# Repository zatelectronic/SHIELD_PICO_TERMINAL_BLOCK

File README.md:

<div align="center">

# SHIELD PICO TERMINAL BLOCK V1

**Shield de expansão para Raspberry Pi Pico com todos os pinos expostos em bornes de parafuso KRE — conexão fácil e robusta sem solda de fios**

</div>

---

## 📋 Índice

- [SHIELD PICO TERMINAL BLOCK V1](#shield-pico-terminal-block-v1)
  - [📋 Índice](#-índice)
  - [Visão Geral](#visão-geral)
  - [Renders 3D](#renders-3d)
  - [Funcionalidades](#funcionalidades)
  - [Mapa Completo de Pinos](#mapa-completo-de-pinos)
    - [J1 — Borne Esquerdo (20 terminais)](#j1--borne-esquerdo-20-terminais)
    - [J2 — Borne Direito (20 terminais)](#j2--borne-direito-20-terminais)
  - [Especificações Técnicas](#especificações-técnicas)
  - [Lista de Materiais](#lista-de-materiais)
  - [Aplicações](#aplicações)
  - [Estrutura do Repositório](#estrutura-do-repositório)
  - [Como Usar](#como-usar)
    - [Instalação](#instalação)
    - [Alimentação](#alimentação)
    - [Exemplo — Piscar LED interno com MicroPython](#exemplo--piscar-led-interno-com-micropython)
    - [Exemplo — Leitura analógica (GP26\_A0)](#exemplo--leitura-analógica-gp26_a0)
    - [Exemplo — I2C com MicroPython](#exemplo--i2c-com-micropython)
    - [Fixação em painel](#fixação-em-painel)
  - [Sobre](#sobre)

---

## Visão Geral

**SHIELD PICO TERMINAL BLOCK V1** é uma placa de expansão para o **Raspberry Pi Pico (RP2040)**, projetada pela **ZAT ELECTRONIC** utilizando **KiCad 10**. O shield encaixa o Raspberry Pi Pico em dois conectores fêmea de 20 pinos e expõe **todos os 40 pinos** do Pico em **dois bornes de parafuso KRE de 20 terminais cada** — um em cada lateral da placa.

O objetivo é simples e prático: eliminar a necessidade de soldar fios diretamente ao Pico, proporcionando **conexões robustas por parafuso** ideais para prototipagem, automação, laboratório e projetos onde os fios precisam ser trocados com frequência.

> 💡 Todos os pinos do Raspberry Pi Pico são acessíveis diretamente pelos bornes — GP0 a GP28, entradas analógicas A0–A2, alimentações VBUS, VSYS, 3V3, GND, ADC_VREF, AGND, 3V3_EN e RUN.

---

## Renders 3D

<div align="center">

*Vista superior — Raspberry Pi Pico encaixado, bornes KRE nas laterais com serigrafias de todos os pinos*

<br/>

*Vista isométrica — bornes de 20 terminais em cada lado e 4 furos de fixação*

</div>

---

## Funcionalidades

- ✅ **Raspberry Pi Pico (RP2040)** — encaixe via 2 conectores fêmea de 20 pinos 2,54mm
- ✅ **Borne KRE J1** — 20 terminais parafuso, lado esquerdo (GP0–GP15 + GNDs)
- ✅ **Borne KRE J2** — 20 terminais parafuso, lado direito (GP16–GP28 + alimentações)
- ✅ **Todos os 40 pinos expostos** — GPIO, analógicos, alimentação e controle
- ✅ **Pinos de alimentação acessíveis** — VBUS, VSYS, 3V3_OUT, 3V3_EN, ADC_VREF, AGND
- ✅ **Pino RUN acessível** — reset externo do Pico por borne
- ✅ **4 furos de fixação** (H1–H4) — montagem em painel ou caixa
- ✅ **Serigrafias completas** — nome de cada pino impresso ao lado do borne correspondente
- ✅ **Sem componentes adicionais** — shield passivo de conexão pura
- ✅ **Made in Brazil** — serigrafia na PCB

---

## Mapa Completo de Pinos

### J1 — Borne Esquerdo (20 terminais)

| Terminal | Pino Pico | Função |
|----------|-----------|--------|
| 1 | GP0 | GPIO / UART0 TX / SPI0 RX / I2C0 SDA / PWM0A |
| 2 | GP1 | GPIO / UART0 RX / SPI0 CSn / I2C0 SCL / PWM0B |
| 3 | GND | Terra |
| 4 | GP2 | GPIO / SPI0 SCK / I2C1 SDA / PWM1A |
| 5 | GP3 | GPIO / SPI0 TX / I2C1 SCL / PWM1B |
| 6 | GP4 | GPIO / UART1 TX / SPI0 RX / I2C0 SDA / PWM2A |
| 7 | GP5 | GPIO / UART1 RX / SPI0 CSn / I2C0 SCL / PWM2B |
| 8 | GND | Terra |
| 9 | GP6 | GPIO / SPI0 SCK / I2C1 SDA / PWM3A |
| 10 | GP7 | GPIO / SPI0 TX / I2C1 SCL / PWM3B |
| 11 | GP8 | GPIO / UART1 TX / SPI1 RX / I2C0 SDA / PWM4A |
| 12 | GP9 | GPIO / UART1 RX / SPI1 CSn / I2C0 SCL / PWM4B |
| 13 | GND | Terra |
| 14 | GP10 | GPIO / SPI1 SCK / I2C1 SDA / PWM5A |
| 15 | GP11 | GPIO / SPI1 TX / I2C1 SCL / PWM5B |
| 16 | GP12 | GPIO / SPI1 RX / I2C0 SDA / PWM6A |
| 17 | GP13 | GPIO / SPI1 CSn / I2C0 SCL / PWM6B |
| 18 | GND | Terra |
| 19 | GP14 | GPIO / SPI1 SCK / I2C1 SDA / PWM7A |
| 20 | GP15 | GPIO / SPI1 TX / I2C1 SCL / PWM7B |

### J2 — Borne Direito (20 terminais)

| Terminal | Pino Pico | Função |
|----------|-----------|--------|
| 1 | VBUS | 5V USB (do conector micro-USB do Pico) |
| 2 | VSYS | Tensão de entrada do sistema (1,8V–5,5V) |
| 3 | GND | Terra |
| 4 | 3V3_EN | Habilita regulador 3,3V interno |
| 5 | 3V3_OUT | Saída 3,3V regulada (até 300mA) |
| 6 | ADC_VREF | Referência de tensão para ADC |
| 7 | GP28_A2 | GPIO / ADC canal 2 |
| 8 | AGND | Terra analógico |
| 9 | GP27_A1 | GPIO / ADC canal 1 / I2C1 SCL |
| 10 | GP26_A0 | GPIO / ADC canal 0 / I2C1 SDA |
| 11 | RUN | Reset externo (ativo em LOW) |
| 12 | GP22 | GPIO / PWM |
| 13 | GND | Terra |
| 14 | GP21 | GPIO / I2C0 SCL / PWM |
| 15 | GP20 | GPIO / I2C0 SDA / PWM |
| 16 | GP19 | GPIO / SPI0 TX / I2C1 SCL / PWM |
| 17 | GP18 | GPIO / SPI0 SCK / I2C1 SDA / PWM |
| 18 | GND | Terra |
| 19 | GP17 | GPIO / UART0 RX / SPI0 CSn / I2C0 SCL / PWM |
| 20 | GP16 | GPIO / UART0 TX / SPI0 RX / I2C0 SDA / PWM |

---

## Especificações Técnicas

| Parâmetro | Valor |
|-----------|-------|
| **Microcontrolador suportado** | Raspberry Pi Pico (RP2040) |
| **Conectores do Pico** | 2x fêmea 20 pinos 2,54mm |
| **Bornes de parafuso** | 2x KRE 20 pinos, passo 5,0mm |
| **Total de terminais** | 40 (todos os pinos do Pico) |
| **Furos de fixação** | 4x (H1–H4) |
| **Componentes ativos** | Nenhum — shield passivo |
| **Ferramenta de Projeto** | KiCad 10 |
| **Versão** | V1 — 2025 |

---

## Lista de Materiais

| Ref | Componente | Valor / Parte | Encapsulamento |
|-----|-----------|--------------|----------------|
| U1 | Raspberry Pi Pico | RP2040 | Módulo — encaixe fêmea 2×20 pinos |
| J1 | Borne Esquerdo | 20 terminais parafuso | KRE 20 pinos, passo 5,0mm |
| J2 | Borne Direito | 20 terminais parafuso | KRE 20 pinos, passo 5,0mm |
| H1–H4 | Furos de Fixação | M3 | MountingHole |

---

## Aplicações

- 🤖 **Automação e controle** — conexão rápida de sensores, atuadores e módulos
- 🏭 **Protótipos industriais** — terminais parafuso para ambientes com vibração
- 🔬 **Laboratório e bancada** — troca rápida de fios sem dessoldagem
- 🏠 **Automação residencial** — integração com relés, sensores e periféricos
- 📡 **IoT com MicroPython** — acesso fácil a todos os pinos para projetos IoT
- 🎓 **Ensino e aprendizado** — plataforma didática para explorar o Raspberry Pi Pico
- 🔧 **Desenvolvimento embarcado** — prototipagem ágil com conexões seguras

---

## Estrutura do Repositório

```
SHIELD_PICO_TERMINAL_BLOCK/
├── SHIELD_PICO_TERMINAL_BLOCK.kicad_pro   # Arquivo de projeto KiCad 10
├── SHIELD_PICO_TERMINAL_BLOCK.kicad_sch   # Esquemático: capa A2 (índice das folhas)
├── PICO.kicad_sch                         # Folha 02: Raspberry Pi Pico + furos M3
├── BORNES.kicad_sch                       # Folha 03: bornes J1 / J2
├── SHIELD_PICO_TERMINAL_BLOCK.kicad_pcb   # Layout da PCB (KiCad 10)
├── SHIELD_PICO_TERMINAL_BLOCK.kicad_prl   # Configurações locais
├── SHIELD_PICO_TERMINAL_BLOCK.kicad_dru   # Regras customizadas (vazio: version 1)
├── Zat_TitleBlock.kicad_wks               # Title block ZAT ELECTRONIC
├── packages3D/                            # Modelos 3D arquivados (referência)
│   ├── raspberry pi pico with contacts.step
│   ├── 20-Pin Header - Female - 2.54mm.step
│   └── DG306-5.0-20P-12-00AH.step
├── imagem_1.png                           # Render 3D superior
├── imagem_2.png                           # Render 3D isométrico
├── LEIA-ME_REVISAO_R01.md                 # O que mudou na revisão R01
└── README.md
```

---

## Como Usar

### Instalação

1. Encaixe o **Raspberry Pi Pico** nos dois conectores fêmea de 20 pinos do shield
2. Certifique-se de que o Pico está bem assentado e alinhado
3. Conecte os fios nos bornes de parafuso desejados, apertando o parafuso com chave de fenda

### Alimentação

| Método | Conexão |
|--------|---------|
| **Via USB do Pico** | Conecte o cabo micro-USB diretamente ao Pico |
| **Via VSYS** | Aplique 1,8V–5,5V no terminal VSYS do borne J2 |
| **Via VBUS** | Aplique 5V no terminal VBUS do borne J2 |

### Exemplo — Piscar LED interno com MicroPython

```python
from machine import Pin
from time import sleep

led = Pin(25, Pin.OUT)  # LED interno do Pico (GP25)

while True:
    led.toggle()
    sleep(0.5)
```

### Exemplo — Leitura analógica (GP26_A0)

```python
from machine import ADC
from time import sleep

adc = ADC(26)  # GP26 = ADC canal 0 (terminal J2 — GP26_A0)

while True:
    valor = adc.read_u16()
    tensao = valor * 3.3 / 65535
    print(f"ADC: {valor} | Tensão: {tensao:.2f}V")
    sleep(0.5)
```

### Exemplo — I2C com MicroPython

```python
from machine import I2C, Pin

# I2C0 em GP0 (SDA) e GP1 (SCL) — terminais J1
i2c = I2C(0, sda=Pin(0), scl=Pin(1), freq=400000)
dispositivos = i2c.scan()
print("Dispositivos I2C encontrados:", [hex(d) for d in dispositivos])
```

### Fixação em painel

> 🔧 Utilize os 4 furos de fixação (H1–H4) com parafusos M3 para montar o shield em painéis, trilhos DIN (com adaptador) ou caixas de projeto.

---

## Sobre

<div align="center">

Projetado por **ZAT ELECTRONIC**

*SHIELD PICO TERMINAL BLOCK V1 — 2025 — Made in Brazil 🇧🇷*

</div>

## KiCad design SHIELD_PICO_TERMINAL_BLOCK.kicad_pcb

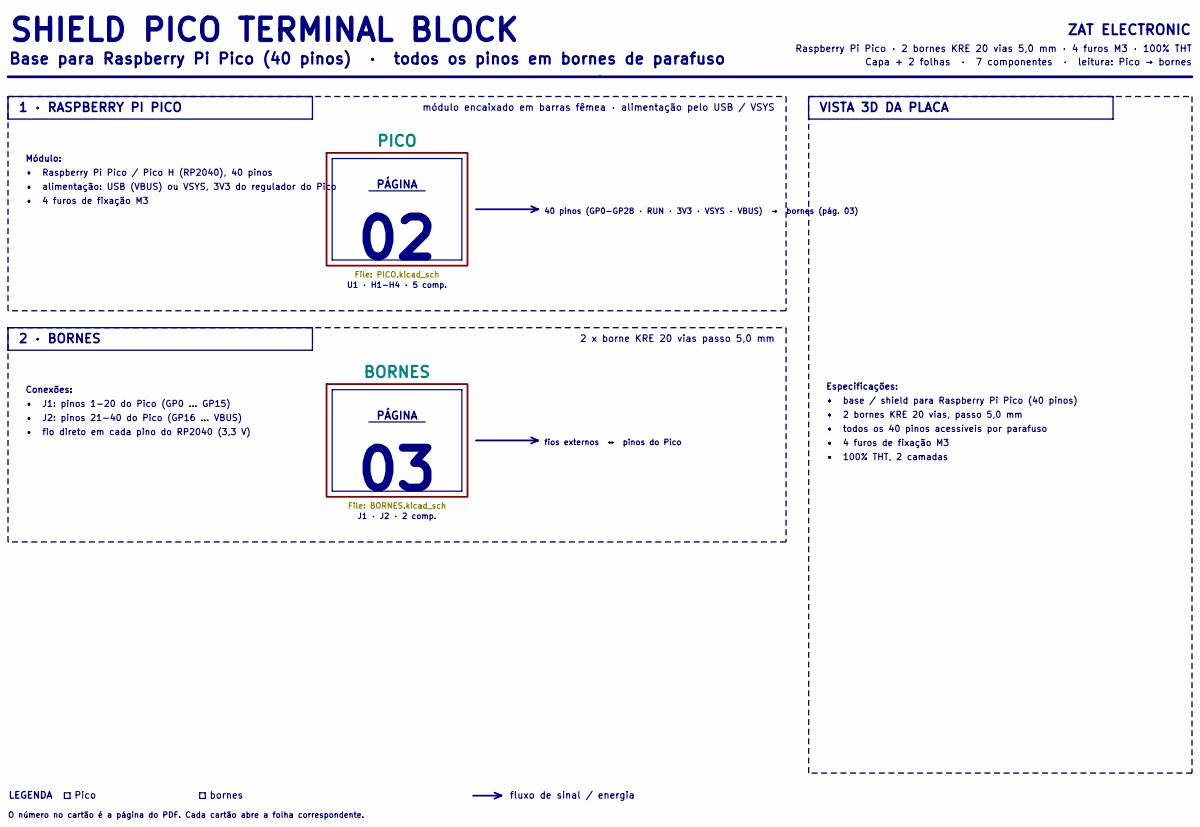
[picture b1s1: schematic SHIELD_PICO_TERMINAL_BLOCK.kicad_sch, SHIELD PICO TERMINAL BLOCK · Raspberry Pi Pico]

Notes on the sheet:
• J1: pinos 1-20 do Pico (GP0 ... GP15)
Módulo:
U1 · H1-H4 · 5 comp.
O número no cartão é a página do PDF. Cada cartão abre a folha correspondente.
• fio direto em cada pino do RP2040 (3,3 V)
Pico
SHIELD PICO TERMINAL BLOCK
Capa + 2 folhas · 7 componentes · leitura: Pico → bornes
2 x borne KRE 20 vias passo 5,0 mm
• base / shield para Raspberry Pi Pico (40 pinos)
ZAT ELECTRONIC
2 · BORNES
bornes
• J2: pinos 21-40 do Pico (GP16 ... VBUS)
Conexões:
fluxo de sinal / energia
• todos os 40 pinos acessíveis por parafuso
• alimentação: USB (VBUS) ou VSYS, 3V3 do regulador do Pico
PÁGINA
• 4 furos de fixação M3
J1 · J2 · 2 comp.
VISTA 3D DA PLACA
LEGENDA
Base para Raspberry Pi Pico (40 pinos) · todos os pinos em bornes de parafuso
módulo encaixado em barras fêmea · alimentação pelo USB / VSYS
• Raspberry Pi Pico / Pico H (RP2040), 40 pinos
Especificações:
Raspberry Pi Pico · 2 bornes KRE 20 vias 5,0 mm · 4 furos M3 · 100% THT
• 2 bornes KRE 20 vias, passo 5,0 mm
fios externos ↔ pinos do Pico
1 · RASPBERRY PI PICO
• 100% THT, 2 camadas
40 pinos (GP0-GP28 · RUN · 3V3 · VSYS · VBUS) → bornes (pág. 03)

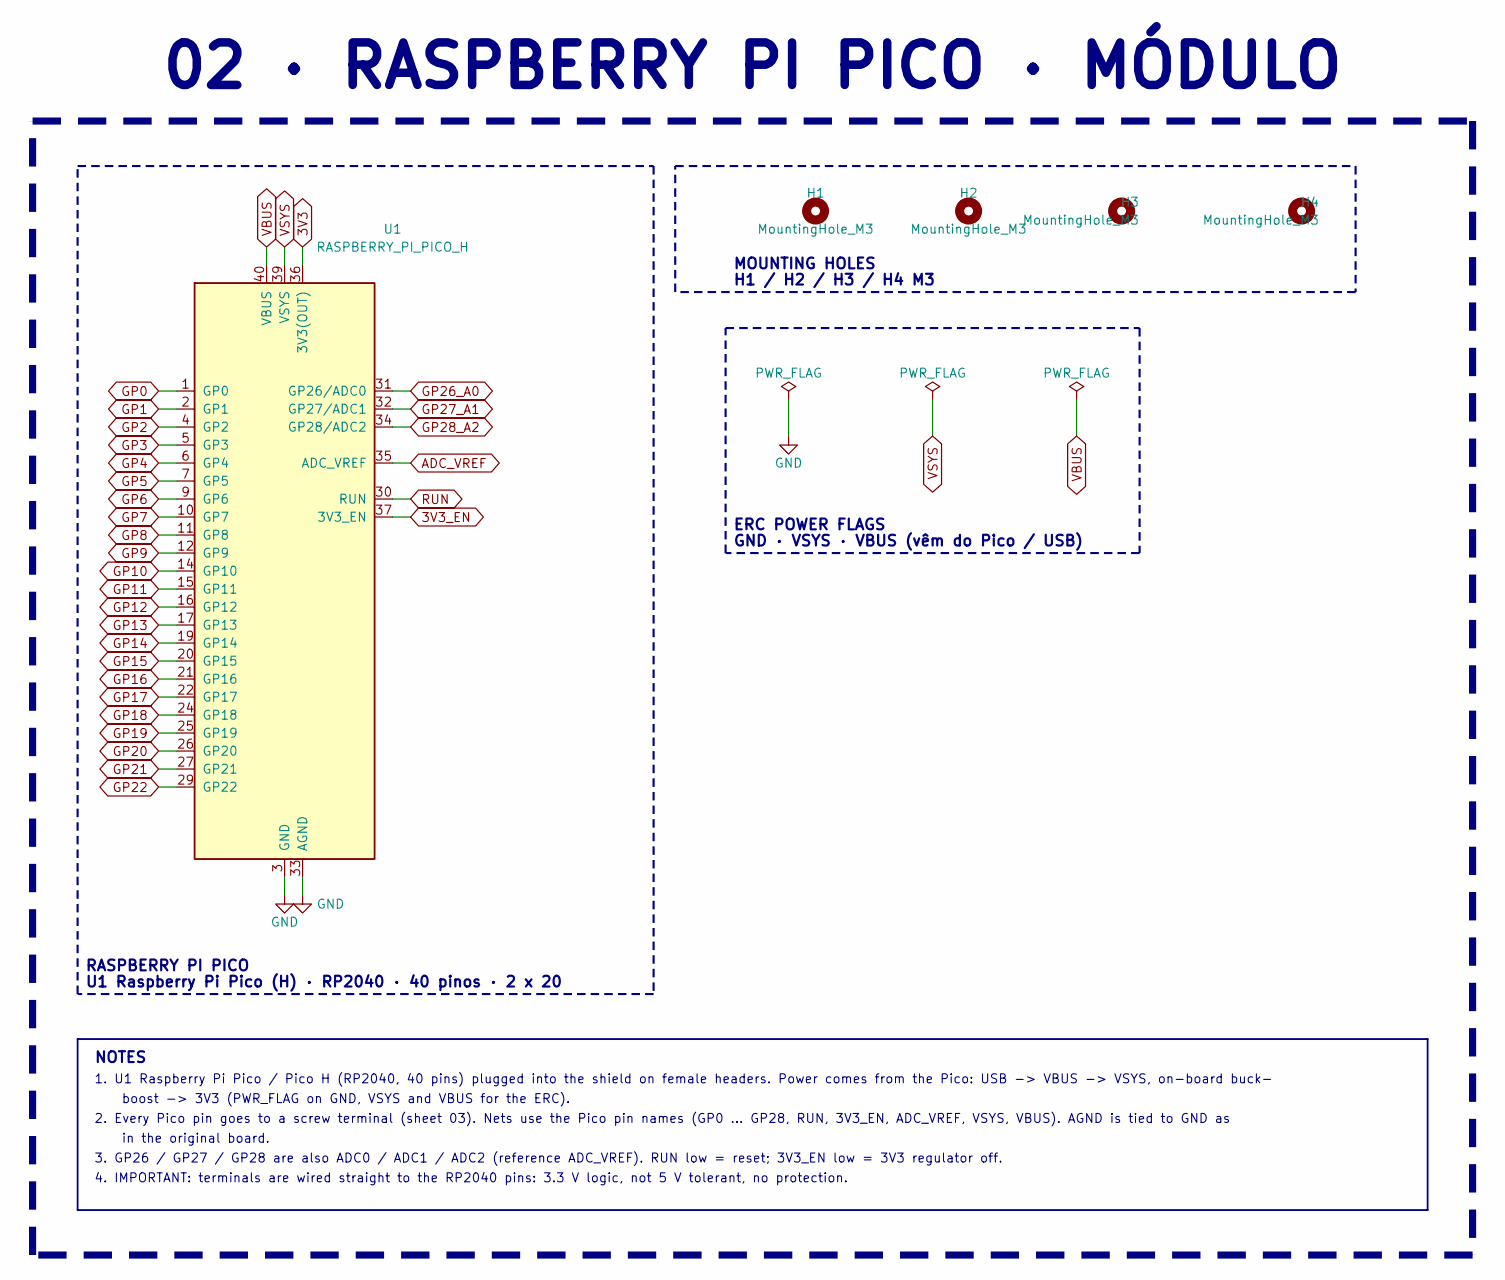
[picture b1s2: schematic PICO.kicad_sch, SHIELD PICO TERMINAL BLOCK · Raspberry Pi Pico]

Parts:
H1, H2, H3, H4: MountingHole_M3; MountingHole_3.2mm_M3_ISO14580
U1: RASPBERRY_PI_PICO_H; MPN Raspberry Pi Pico H (SC0917)

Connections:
3V3: U1.36 (3V3(OUT)); also elsewhere on the board
3V3_EN: U1.37 (3V3_EN); also elsewhere on the board
ADC_VREF: U1.35 (ADC_VREF); also elsewhere on the board
GND: U1.3 (GND), U1.8 (GND), U1.13 (GND), U1.18 (GND), U1.23 (GND), U1.28 (GND), U1.33 (AGND), U1.38 (GND); also elsewhere on the board
GP0: U1.1 (GP0); also elsewhere on the board
GP1: U1.2 (GP1); also elsewhere on the board
GP2: U1.4 (GP2); also elsewhere on the board
GP3: U1.5 (GP3); also elsewhere on the board
GP4: U1.6 (GP4); also elsewhere on the board
GP5: U1.7 (GP5); also elsewhere on the board
GP6: U1.9 (GP6); also elsewhere on the board
GP7: U1.10 (GP7); also elsewhere on the board
GP8: U1.11 (GP8); also elsewhere on the board
GP9: U1.12 (GP9); also elsewhere on the board
GP10: U1.14 (GP10); also elsewhere on the board
GP11: U1.15 (GP11); also elsewhere on the board
GP12: U1.16 (GP12); also elsewhere on the board
GP13: U1.17 (GP13); also elsewhere on the board
GP14: U1.19 (GP14); also elsewhere on the board
GP15: U1.20 (GP15); also elsewhere on the board
GP16: U1.21 (GP16); also elsewhere on the board
GP17: U1.22 (GP17); also elsewhere on the board
GP18: U1.24 (GP18); also elsewhere on the board
GP19: U1.25 (GP19); also elsewhere on the board
GP20: U1.26 (GP20); also elsewhere on the board
GP21: U1.27 (GP21); also elsewhere on the board
GP22: U1.29 (GP22); also elsewhere on the board
GP26_A0: U1.31 (GP26/ADC0); also elsewhere on the board
GP27_A1: U1.32 (GP27/ADC1); also elsewhere on the board
GP28_A2: U1.34 (GP28/ADC2); also elsewhere on the board
RUN: U1.30 (RUN); also elsewhere on the board
VBUS: U1.40 (VBUS); also elsewhere on the board
VSYS: U1.39 (VSYS); also elsewhere on the board

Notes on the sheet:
U1 Raspberry Pi Pico (H) · RP2040 · 40 pinos · 2 x 20
02 · RASPBERRY PI PICO · MÓDULO
boost -> 3V3 (PWR_FLAG on GND, VSYS and VBUS for the ERC).
1. U1 Raspberry Pi Pico / Pico H (RP2040, 40 pins) plugged into the shield on female headers. Power comes from the Pico: USB -> VBUS -> VSYS, on-board buck-
3. GP26 / GP27 / GP28 are also ADC0 / ADC1 / ADC2 (reference ADC_VREF). RUN low = reset; 3V3_EN low = 3V3 regulator off.
4. IMPORTANT: terminals are wired straight to the RP2040 pins: 3.3 V logic, not 5 V tolerant, no protection.
NOTES
2. Every Pico pin goes to a screw terminal (sheet 03). Nets use the Pico pin names (GP0 ... GP28, RUN, 3V3_EN, ADC_VREF, VSYS, VBUS). AGND is tied to GND as
GND · VSYS · VBUS (vêm do Pico / USB)
H1 / H2 / H3 / H4 M3
in the original board.
MOUNTING HOLES
RASPBERRY PI PICO
ERC POWER FLAGS

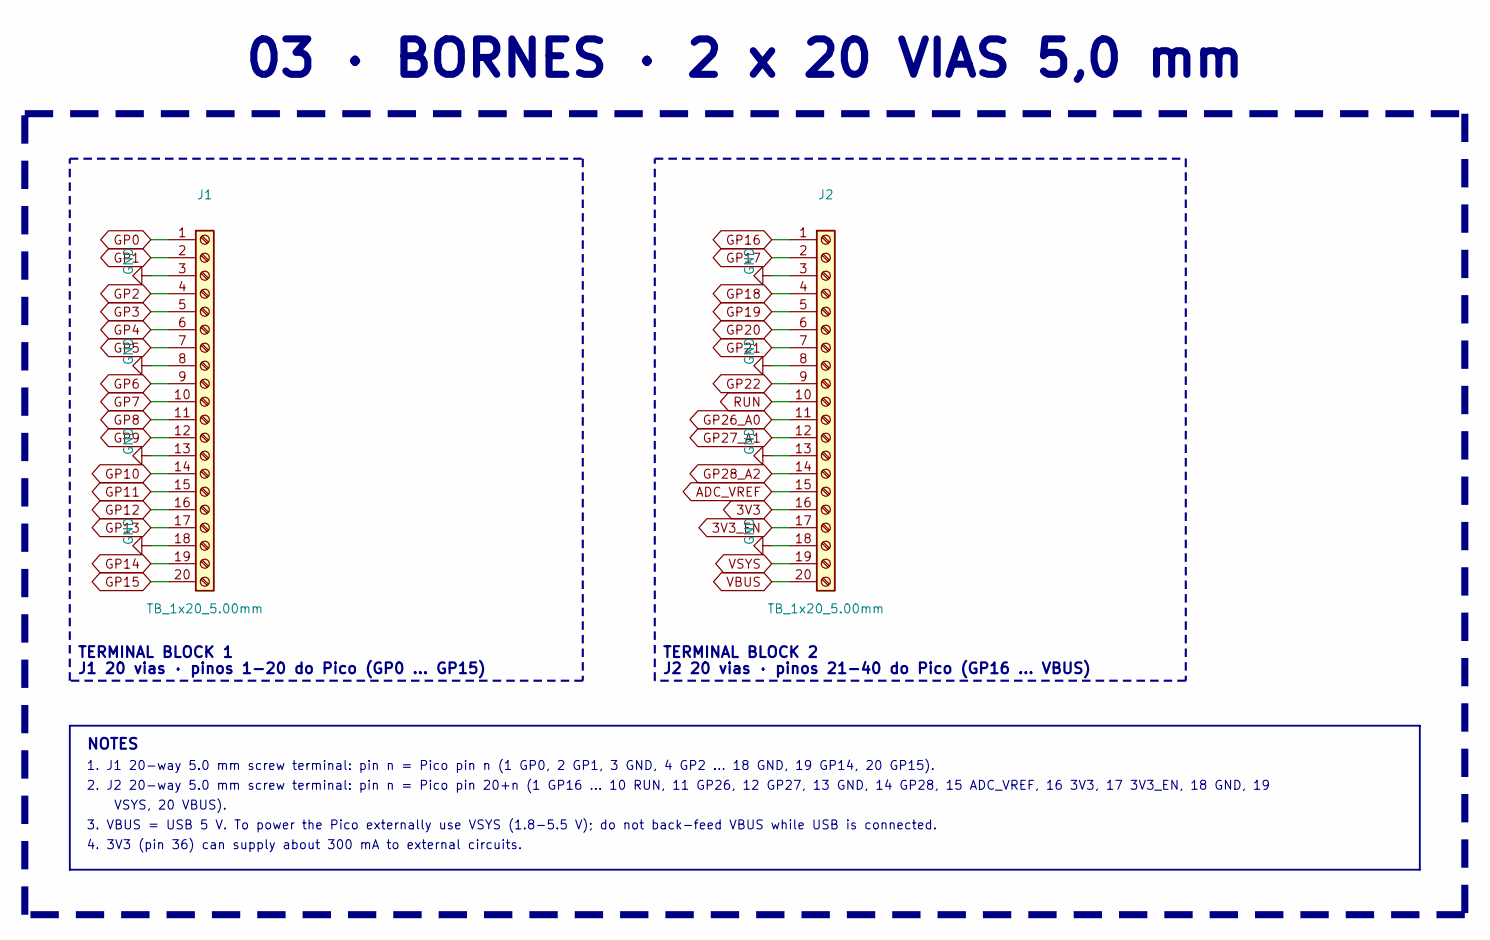
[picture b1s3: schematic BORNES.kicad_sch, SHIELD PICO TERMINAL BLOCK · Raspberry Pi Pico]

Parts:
J1, J2: TB_1x20_5.00mm; TerminalBlock_MaiXu_MX126-5.0-20P_1x20_P5.00mm_DG306_EdgeMo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

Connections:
3V3: J2.16; also elsewhere on the board
3V3_EN: J2.17; also elsewhere on the board
ADC_VREF: J2.15; also elsewhere on the board
GND: J1.3, J1.8, J1.13, J1.18, J2.3, J2.8, J2.13, J2.18; also elsewhere on the board
GP0: J1.1; also elsewhere on the board
GP1: J1.2; also elsewhere on the board
GP2: J1.4; also elsewhere on the board
GP3: J1.5; also elsewhere on the board
GP4: J1.6; also elsewhere on the board
GP5: J1.7; also elsewhere on the board
GP6: J1.9; also elsewhere on the board
GP7: J1.10; also elsewhere on the board
GP8: J1.11; also elsewhere on the board
GP9: J1.12; also elsewhere on the board
GP10: J1.14; also elsewhere on the board
GP11: J1.15; also elsewhere on the board
GP12: J1.16; also elsewhere on the board
GP13: J1.17; also elsewhere on the board
GP14: J1.19; also elsewhere on the board
GP15: J1.20; also elsewhere on the board
GP16: J2.1; also elsewhere on the board
GP17: J2.2; also elsewhere on the board
GP18: J2.4; also elsewhere on the board
GP19: J2.5; also elsewhere on the board
GP20: J2.6; also elsewhere on the board
GP21: J2.7; also elsewhere on the board
GP22: J2.9; also elsewhere on the board
GP26_A0: J2.11; also elsewhere on the board
GP27_A1: J2.12; also elsewhere on the board
GP28_A2: J2.14; also elsewhere on the board
RUN: J2.10; also elsewhere on the board
VBUS: J2.20; also elsewhere on the board
VSYS: J2.19; also elsewhere on the board

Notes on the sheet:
1. J1 20-way 5.0 mm screw terminal: pin n = Pico pin n (1 GP0, 2 GP1, 3 GND, 4 GP2 ... 18 GND, 19 GP14, 20 GP15).
4. 3V3 (pin 36) can supply about 300 mA to external circuits.
TERMINAL BLOCK 2
TERMINAL BLOCK 1
2. J2 20-way 5.0 mm screw terminal: pin n = Pico pin 20+n (1 GP16 ... 10 RUN, 11 GP26, 12 GP27, 13 GND, 14 GP28, 15 ADC_VREF, 16 3V3, 17 3V3_EN, 18 GND, 19
VSYS, 20 VBUS).
3. VBUS = USB 5 V. To power the Pico externally use VSYS (1.8-5.5 V); do not back-feed VBUS while USB is connected.
J2 20 vias · pinos 21-40 do Pico (GP16 ... VBUS)
03 · BORNES · 2 x 20 VIAS 5,0 mm
J1 20 vias · pinos 1-20 do Pico (GP0 ... GP15)
NOTES

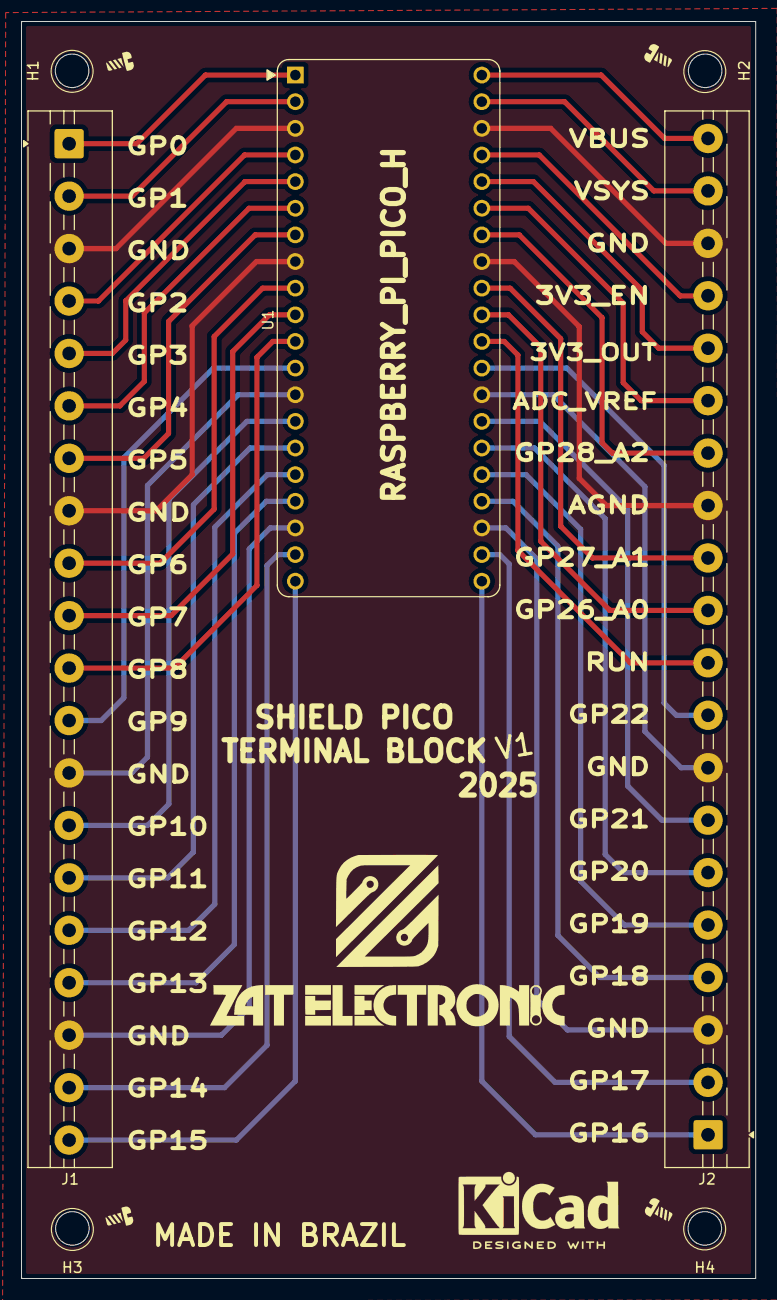
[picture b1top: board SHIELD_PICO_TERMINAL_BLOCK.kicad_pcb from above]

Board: 2 copper layers, 70.0 x 119.8 mm, 7 parts (0 on the bottom side), 33 nets.

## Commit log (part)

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2026-06-03 COMMIT-02-06-26
2026-06-28 commit_3
2026-06-29 COMMIT-4
